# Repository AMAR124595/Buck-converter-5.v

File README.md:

# Custom 5V Power Supply Circuit

A professionally designed **5V buck converter power supply** built around the [Texas Instruments TPS5430](https://www.ti.com/product/TPS5430).  
This circuit ensures a **stable and efficient 5V output** under varying load conditions, making it ideal for embedded systems, IoT projects, and other electronics requiring reliable regulation.

---

## 📖 Overview
This project provides a custom-designed **5V DC power supply module** implemented in Kicad **[Pictures ](https://github.com/AMAR124595/Buck-converter-5.v/tree/master/Image)**.  
It is optimized to deliver **up to 3A continuous output current** from a lithium battery pack (2S2P, 7.4V nominal) or other DC sources within the supported input range.

---

## ✨ Features
- ✅ Input voltage range: **6V – 36V** (tested with 2S Li-ion pack, 7.4V nominal, 8.4V max)  
- ✅ Regulated **5V output**, capable of delivering up to **3A**  
- ✅ Based on **TI TPS5430 step-down (buck) converter**  
- ✅ Incorporates **low-ESR polymer capacitor** for stable ripple performance  
- ✅ Compact SMD layout with optimized PCB grounding for thermal and electrical efficiency  
- ✅ Ideal for powering **ESP32, microcontrollers, sensors, and small audio circuits**

---

## ⚙️ How It Works
1. **Input Power**  
   - The circuit accepts power from a  DC supplies up to 35V.  

2. **Buck Conversion (TPS5430)**  
   - The TPS5430 regulator steps down the input voltage to a stable 5V output.  
   - Switching frequency and inductor values are chosen for efficiency and low ripple.  

3. **Output Filtering**  
   - A combination of **ceramic capacitors** (high-frequency filtering) and a **bulk polymer capacitor (220µF, low ESR)** ensures clean output with minimal voltage ripple.  

4. **Enable Pin (EN)**  
   - Left floating by default → device enabled automatically.  
   - Can be tied to logic-level signals for power sequencing if required.  

---

## 🛠️ Tools Used
- **Schematic & PCB Design:** [The entire design and simulation process was completed using KiCad](https://github.com/AMAR124595/Buck-converter-5.v/tree/master) 
- **Datasheet Reference:** [Texas Instruments TPS5430 Datasheet](https://www.ti.com/lit/ds/symlink/tps5430.pdf)  
- **Simulation & Validation:** TI Webench, vendor application notes  
- **BOM Management:** Digi-Key / Mouser / Robu.in  

---

## 🧾 Component List (BOM)

Below is the list of major components used in this custom 5V power supply design:

| Component | Value / Spec | Package | Link |
|-----------|--------------|---------|------|
| C1        | 10 µF, 50V, X7R MLCC | 1210 | [Samsung CL32B106KBJNNWE](https://robu.in/product/cl32b106kbjnnwe-samsang-50v-10uf-x7r-%C2%B110-1210-multilayer-ceramic-capacitors-mlcc-smd-smt-rohs/?) |
| L1        | 15 µH, 3A (4A peak), Shielded Inductor | SRP7028CC | [Bourns SRP7028CC-150M](https://robu.in/product/srp7028cc-150m-bourns-srp7028cc-150m-power-inductor-smd-15-%C2%B5h-3-a-shielded-4-a-srp7028cc-series/?) |
| D1        | Schottky Diode, 40V, 3A | DO-214AC (SMA) | [Vishay B340A-E3/5AT](https://robu.in/product/b340a-e3-5at-vishay-intertech-40v-3a-550mv3a-do-214acsma-schottky-diodes-rohs/?) |
| C2        | 0.01 µF, 50V, C0G | 0805 | [Samsung CL21C103JBFNNNE](https://robu.in/product/cl21c103jbfnnne-samsung-cap-ceramic-0-01uf-50v-c0g-5-pad-smd-0805-125c-t-r/?) |
| U1        | DC-DC Buck Converter IC | SO PowerPAD-8 | [TI TPS5430DDAR](https://robu.in/product/tps5430ddar-so-powerpad-8-dc-dc-buck-step-down-switching-voltage-regulators/) |
| R1        | 3.24 kΩ, 1%, 0603 | 0603 | [Uniohm 0603WAF3241T5E](https://robu.in/product/0603waf3241t5e-uniohm-royal-ohm-100mw-thick-film-resistors-75v-%C2%B1100ppm-%E2%84%83%C2%B11-3-24k%CF%89-0603-chip-resistor-surface-mount-rohs/) |
| R2        | 10 kΩ, 1%, 0603 | 0603 | [0603 SMD Resistor Pack](https://robu.in/product/10k-ohm-1-4w-0603-surface-mount-chip-resistor-pack-of-100/?) |
| C3        | 220 µF, 10V, Low-ESR Polymer Capacitor | 2917 (7343) | [Panasonic 10TPB220M](https://www.digikey.com/en/products/detail/panasonic-electronic-components/10TPB220M/4204779) |

---

## 👤 Author
**Amar Gangadhar A (SenseAbility innovations pvt.ltd)**  
Electronics Engineer | Embedded Systems Designer |   Embedded Firmware Developer

---

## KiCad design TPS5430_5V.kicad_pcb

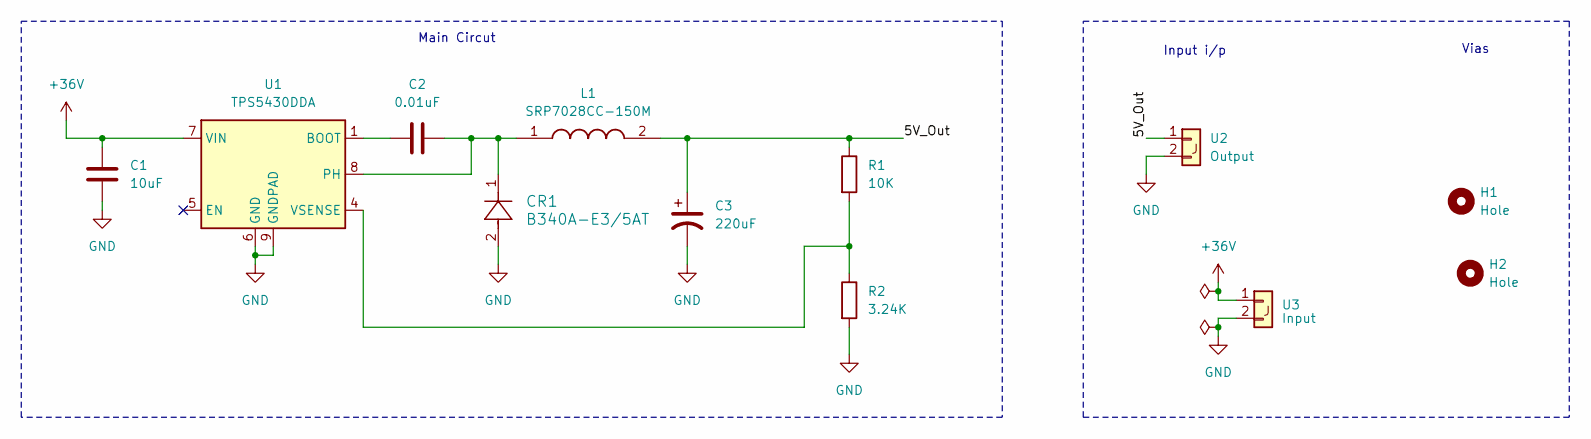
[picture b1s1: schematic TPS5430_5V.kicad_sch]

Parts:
C1: 10uF; C_1210_3225Metric_Pad1.33x2.70mm_HandSolder
C2: 0.01uF; C_0805_2012Metric_Pad1.18x1.45mm_HandSolder
C3: 220uF; CP_EIA-7343-40_Kemet-Y_Pad2.25x2.55mm_HandSolder
CR1: B340A-E3/5AT; CR_0A-E3&slash_5AT_VIS
H1, H2: Hole; MountingHole_2.7mm_M2.5
L1: SRP7028CC-150M; INDPM7366X300N; Mouser Part Number 652-SRP7028CC-150M
R1: 10K; R_0603_1608Metric_Pad0.98x0.95mm_HandSolder
R2: 3.24K; R_0603_1608Metric_Pad0.98x0.95mm_HandSolder
U1: TPS5430DDA; TI_SO-PowerPAD-8_ThermalVias
U2: Output; 2-p-connector
U3: Input; 2-p-connector

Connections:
+36V: C1.1, U1.7 (VIN), U3.1
/5V_Out: C3.1, L1.2, R1.1, U2.1
GND: C1.2, C3.2, CR1.2, R2.2, U1.6 (GND), U1.9 (GNDPAD), U2.2, U3.2
unnamed: C2.1, U1.1 (BOOT)
unnamed: C2.2, CR1.1, L1.1, U1.8 (PH)
unnamed: R1.2, R2.1, U1.4 (VSENSE)

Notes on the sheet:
Main Circut
Input i/p
Vias

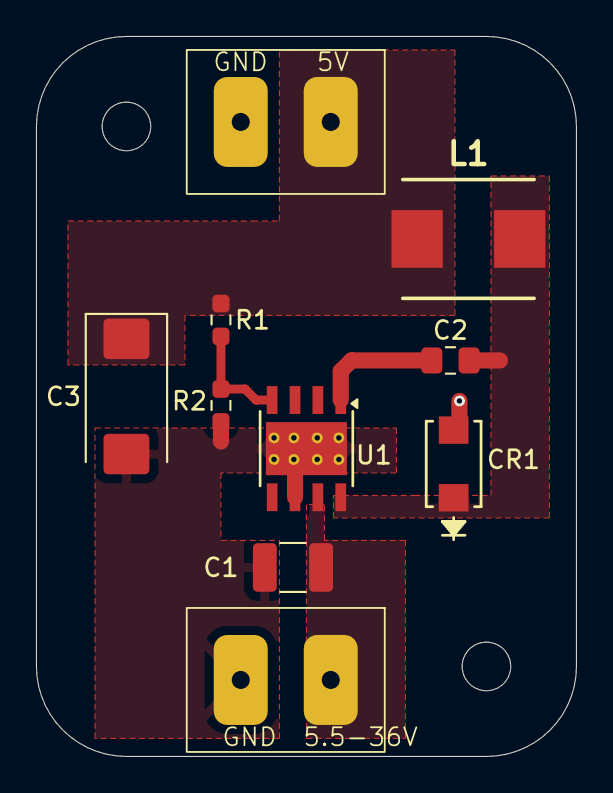
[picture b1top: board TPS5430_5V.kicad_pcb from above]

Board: 2 copper layers, 30.0 x 40.0 mm, 12 parts (0 on the bottom side), 6 nets.

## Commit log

2025-09-17 commit all the files
2025-09-17 Image added
2025-09-17 Image name changed
2025-09-18 New Updation
2025-09-18 Ignore all KiCad project metadata
2025-09-18 Stop tracking KiCad auto-generated files
2025-09-18 Ignore KiCad auto-generated files
